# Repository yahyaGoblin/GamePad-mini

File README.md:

# Split PCB Gamepad

A custom gamepad built on a split PCB design, with two halves connected via a 14-pin ribbon cable connector on each side.
### Schematic Preview

### PCB Preview

### 3D Preview

## Features

- Split PCB — left and right halves connected via ribbon cable
- 14-pin connector on each half
- Compact and ergonomic layout
- USB-C connection to host

## Bill of Materials

| Ref | Component | Value / Model | Qty |
|-----|-----------|---------------|-----|
| U1 | Microcontroller | Pro Micro (ATmega32U4) or RP2040 | 1 |
| SW1–SWn | Mechanical / Tactile Switch | Cherry MX or tactile equiv. | n |
| D1–Dn | Switching Diode | 1N4148 SOD-123 | n |
| J1 | Ribbon Cable Connector (Left) | 14-pin FFC/FPC or IDC | 1 |
| J2 | Ribbon Cable Connector (Right) | 14-pin FFC/FPC or IDC | 1 |
| CABLE1 | Ribbon Cable | 14-pin, length as needed | 1 |
| C1 | Decoupling Capacitor | 100nF 0402 | 1 |

> Update quantities (n) based on your final button layout. Part numbers are suggestions.

## PCB Design

The gamepad is split into two PCBs:
- **Left half** — connected to the host via USB, handles all logic
- **Right half** — communicates to the left half via the 14-pin ribbon cable

Both halves share the same connector footprint on the inner edges.

## Firmware

Compatible with [QMK](https://qmk.fm/) or [KMK](https://github.com/KMKfw/kmk_firmware) with split keyboard support.

## License

Open source hardware — feel free to modify and build your own.

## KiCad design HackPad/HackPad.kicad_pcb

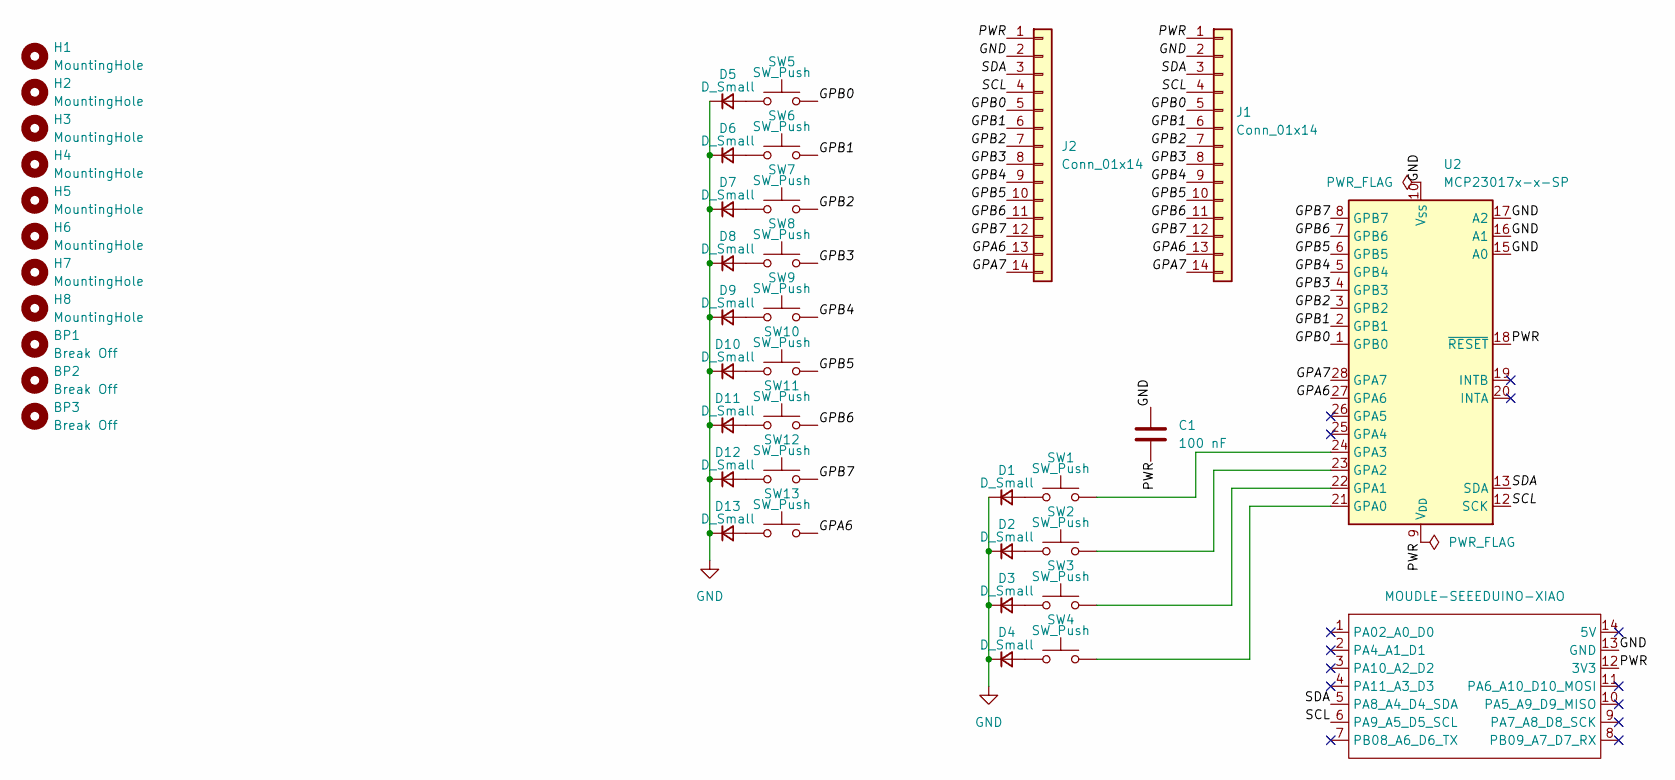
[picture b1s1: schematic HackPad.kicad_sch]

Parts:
BP1, BP2, BP3: Break Off; mouse-bite-2mm-slot
C1: 100 nF; C_0805_2012Metric_Pad1.18x1.45mm_HandSolder
D1, D2, D3, D4, D5, D6, D7, D8, D9, D10, D11, D12, D13: D_Small; D_SOD-123
H1, H2, H3, H4, H5, H6, H7, H8: MountingHole; MountingHole_3.2mm_M3
J1, J2: Conn_01x14; PinHeader_1x14_P2.54mm_Vertical
SW1, SW2, SW3, SW4, SW5, SW6, SW7, SW8, SW9, SW10, SW11, SW12, SW13: SW_Push; SW_Cherry_MX_1.00u_PCB
U1: MOUDLE-SEEEDUINO-XIAO; XIAO-Generic-Hybrid-14P-2.54-21X17.8MM
U2: MCP23017x-x-SP; DIP-28_W7.62mm

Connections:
/GPA6: J1.13, J2.13, SW13.2, U2.27 (GPA6)
/GPA7: J1.14, J2.14, U2.28 (GPA7)
/GPB0: J1.5, J2.5, SW5.2, U2.1 (GPB0)
/GPB1: J1.6, J2.6, SW6.2, U2.2 (GPB1)
/GPB2: J1.7, J2.7, SW7.2, U2.3 (GPB2)
/GPB3: J1.8, J2.8, SW8.2, U2.4 (GPB3)
/GPB4: J1.9, J2.9, SW9.2, U2.5 (GPB4)
/GPB5: J1.10, J2.10, SW10.2, U2.6 (GPB5)
/GPB6: J1.11, J2.11, SW11.2, U2.7 (GPB6)
/GPB7: J1.12, J2.12, SW12.2, U2.8 (GPB7)
/PWR: C1.2, J1.1, J2.1, U1.12 (3V3), U2.9 (V_{DD}), U2.18 (~RESET)
/SCL: J1.4, J2.4, U1.6 (PA9_A5_D5_SCL), U2.12 (SCK)
/SDA: J1.3, J2.3, U1.5 (PA8_A4_D4_SDA), U2.13 (SDA)
GND: C1.1, D1.1 (K), D2.1 (K), D3.1 (K), D4.1 (K), D5.1 (K), D6.1 (K), D7.1 (K), D8.1 (K), D9.1 (K), D10.1 (K), D11.1 (K), D12.1 (K), D13.1 (K), J1.2, J2.2, U1.13 (GND), U2.10 (V_{SS}), U2.15 (A0), U2.16 (A1), U2.17 (A2)
unnamed: D1.2 (A), SW1.1
unnamed: D2.2 (A), SW2.1
unnamed: D3.2 (A), SW3.1
unnamed: D4.2 (A), SW4.1
unnamed: D5.2 (A), SW5.1
unnamed: D6.2 (A), SW6.1
unnamed: D7.2 (A), SW7.1
unnamed: D8.2 (A), SW8.1
unnamed: D9.2 (A), SW9.1
unnamed: D10.2 (A), SW10.1
unnamed: D11.2 (A), SW11.1
unnamed: D12.2 (A), SW12.1
unnamed: D13.2 (A), SW13.1
unnamed: SW4.2, U2.21 (GPA0)
unnamed: SW3.2, U2.22 (GPA1)
unnamed: SW2.2, U2.23 (GPA2)
unnamed: SW1.2, U2.24 (GPA3)

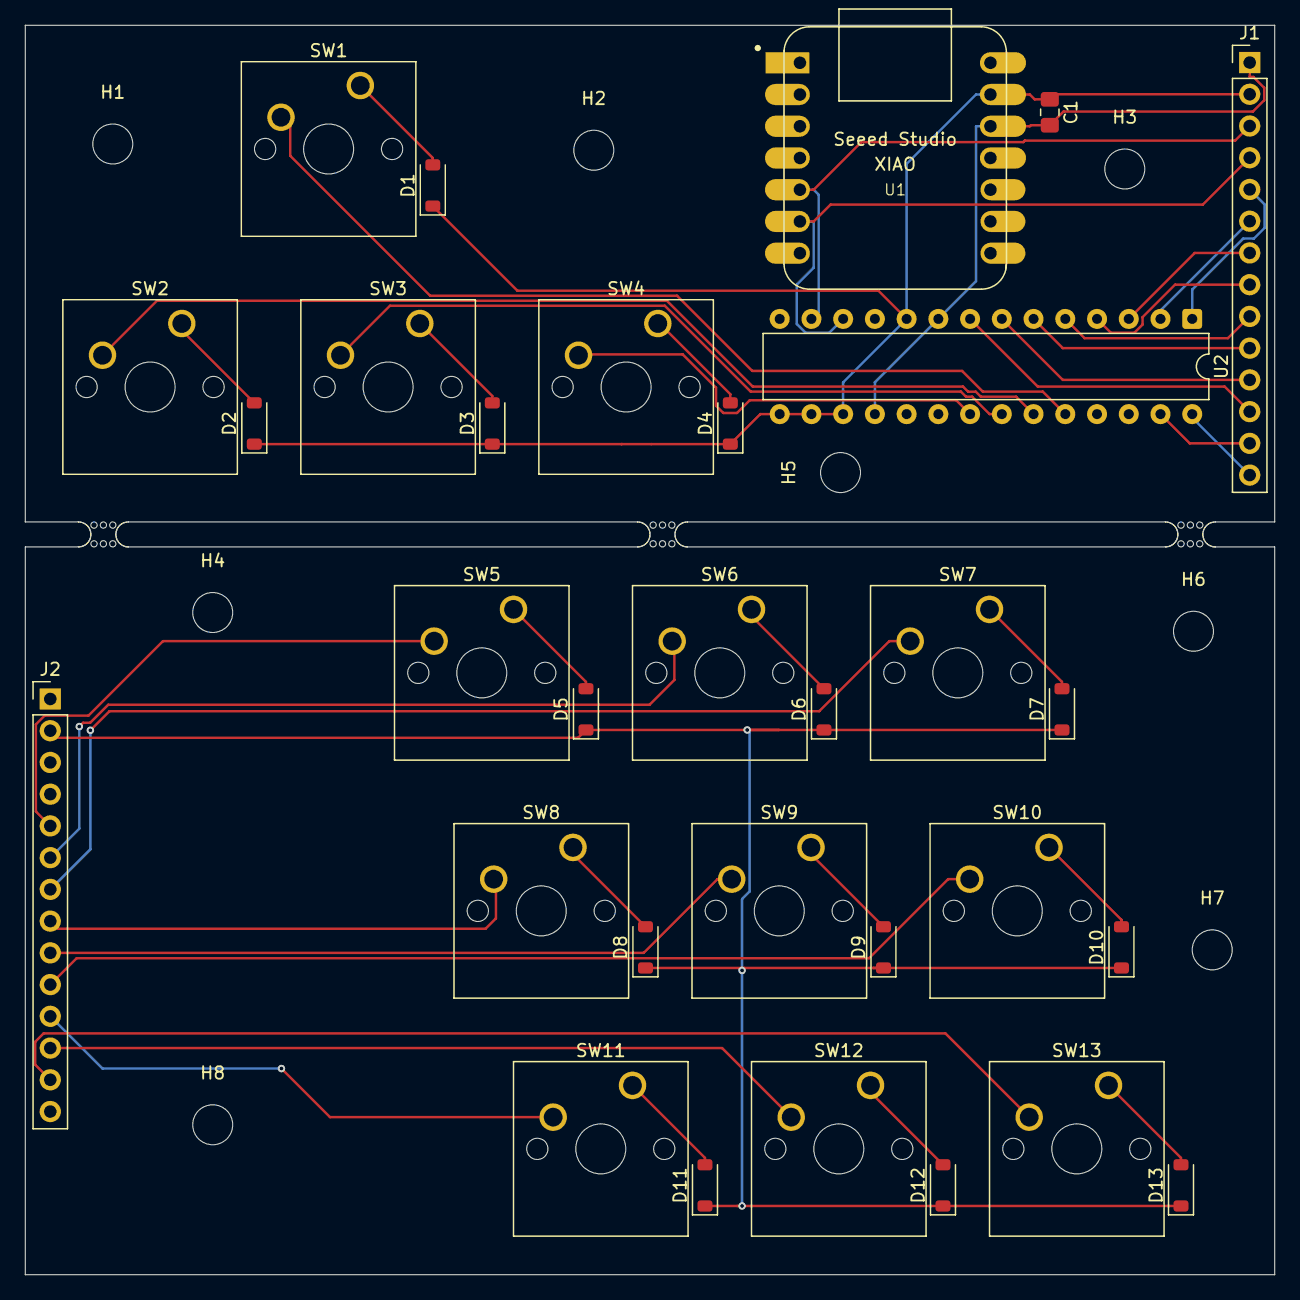
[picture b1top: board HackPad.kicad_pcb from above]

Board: 2 copper layers, 100.0 x 100.0 mm, 42 parts (0 on the bottom side), 31 nets.

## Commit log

2026-05-27 Update README by removing fabrication and project files
    Removed fabrication details and project files section from README.
2026-05-27 Swap PCB and 3D preview images in README
2026-05-29 gerber
